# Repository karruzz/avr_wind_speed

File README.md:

# About

Wind speed measuring

# Board schematic

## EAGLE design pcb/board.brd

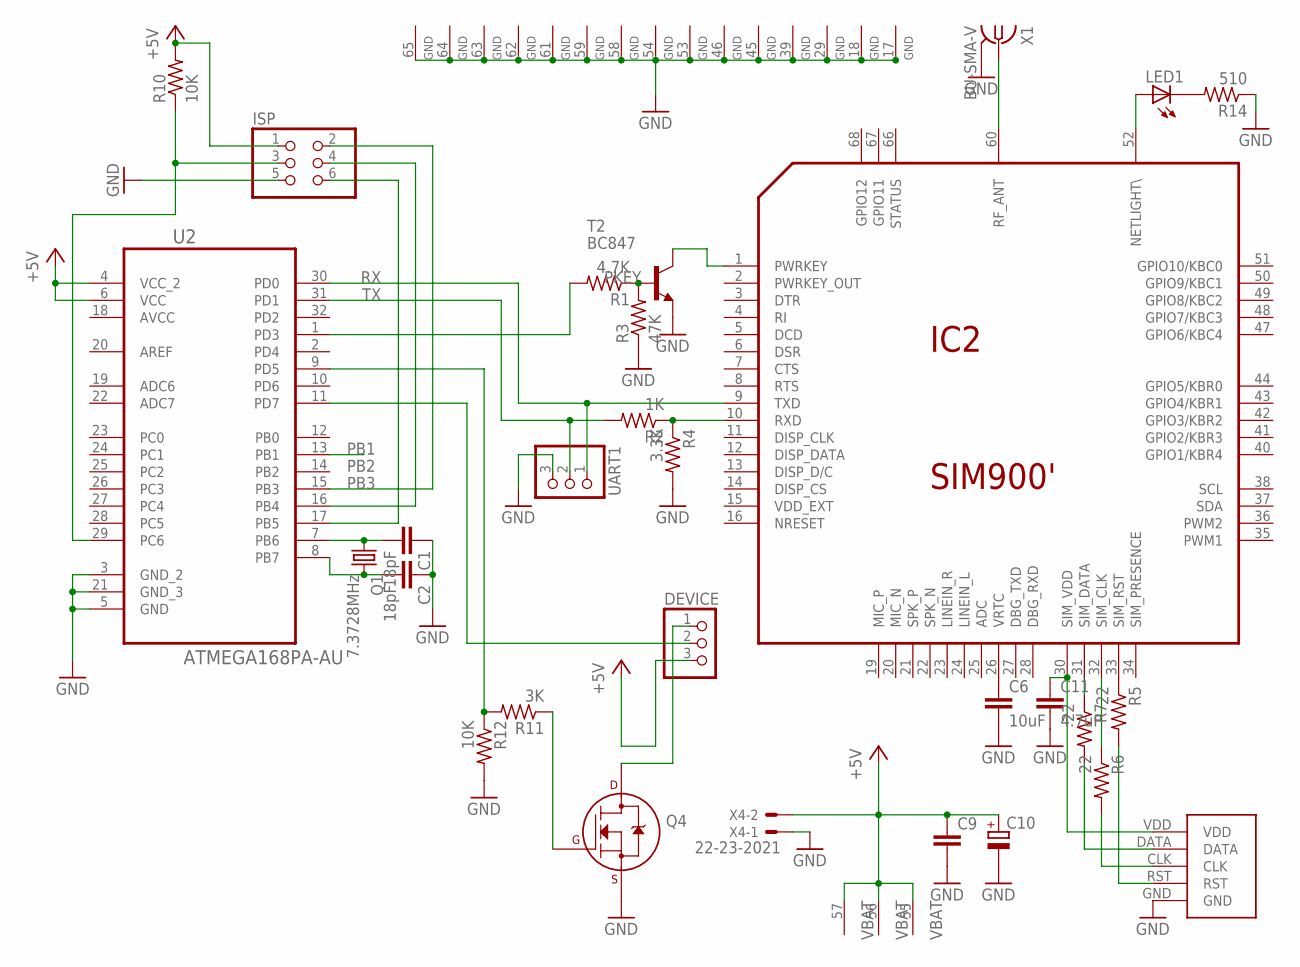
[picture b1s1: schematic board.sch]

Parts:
C1, C2: 18pF; C1206
C6: 10uF; C1206
C9: C-EUC1206K; C1206K
C10: CPOL-EUE5-8.5; E5-8,5
C11: 4.7uF; C1206
DEVICE: PINHD-1X3; 1X03
IC2: SIM900'; SIM900_NARROW
ISP: PINHD-2X3; 2X03
LED1: LED_E; LED_1206
Q1: 7.3728MHz; HC49U-V
Q4: 2N700_SOT23_1; SOT23
R1: 4.7K; R1206
R2: 1K; R1206
R3: 47K; R1206
R4: 3.3K; R1206
R5, R6, R7: 22; R1206
R10, R12: 10K; M1206
R11: 3K; M1206
R14: 510; R1206
SIM_HOLDER: 115B-AAA0-R; C707_10M006_512_2
T2: BC847; SOT23
U2: ATMEGA168PA-AU; QFP80P900X900X120-32N
UART1: PINHD-1X3; 1X03
X1: BU-SMA-V
X4: 22-23-2021

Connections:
+5V: C9.1, C10.+, DEVICE.3, IC2.55 (VBAT), IC2.56 (VBAT), IC2.57 (VBAT), ISP.1, R10.2, U2.4 (VCC_2), U2.6 (VCC), X4.2
AVCC: U2.18 (AVCC)
GND: C1.1, C2.1, C6.2, C9.2, C10.-, C11.2, IC2.17 (GND), IC2.18 (GND), IC2.29 (GND), IC2.39 (GND), IC2.45 (GND), IC2.46 (GND), IC2.53 (GND), IC2.54 (GND), IC2.58 (GND), IC2.59 (GND), IC2.61 (GND), IC2.62 (GND), IC2.63 (GND), IC2.64 (GND), IC2.65 (GND), ISP.5, Q4.2 (S), R3.1, R4.2, R12.2, R14.1, SIM_HOLDER.GND, T2.2 (E), U2.3 (GND_2), U2.5 (GND), U2.21 (GND_3), UART1.3, X1.2, X1.3 (2), X1.4 (2), X1.5 (2), X4.1
unnamed: C1.2, Q1.1, U2.7 (PB6)
unnamed: DEVICE.2, U2.11 (PD7)
unnamed: Q4.1 (G), R11.1
unnamed: ISP.3, R10.1, U2.29 (PC6)
unnamed: ISP.4, U2.16 (PB4)
unnamed: ISP.6, U2.17 (PB5)
unnamed: IC2.1 (PWRKEY), T2.3 (C)
unnamed: IC2.10 (RXD), R2.1, R4.1
unnamed: R1.1, R3.2, T2.1 (B)
unnamed: C2.2, Q1.2, U2.8 (PB7)
unnamed: IC2.52 (NETLIGHT\), LED1.A
unnamed: LED1.C, R14.2
unnamed: R5.2, SIM_HOLDER.RST
unnamed: C11.1, IC2.30 (SIM_VDD), SIM_HOLDER.VDD
unnamed: C6.1, IC2.26 (VRTC)
unnamed: IC2.31 (SIM_DATA), R7.1
unnamed: IC2.32 (SIM_CLK), R6.1
unnamed: IC2.33 (SIM_RST), R5.1
unnamed: R7.2, SIM_HOLDER.DATA
unnamed: IC2.60 (RF_ANT), X1.1
unnamed: DEVICE.1, Q4.3 (D)
unnamed: R6.2, SIM_HOLDER.CLK
PB1: U2.13 (PB1)
PB2: R11.2, R12.1, U2.9 (PD5)
PB3: ISP.2, U2.15 (PB3)
PKEY: R1.2, U2.1 (PD3)
RX: IC2.9 (TXD), U2.30 (PD0), UART1.1
TX: R2.2, U2.31 (PD1), UART1.2

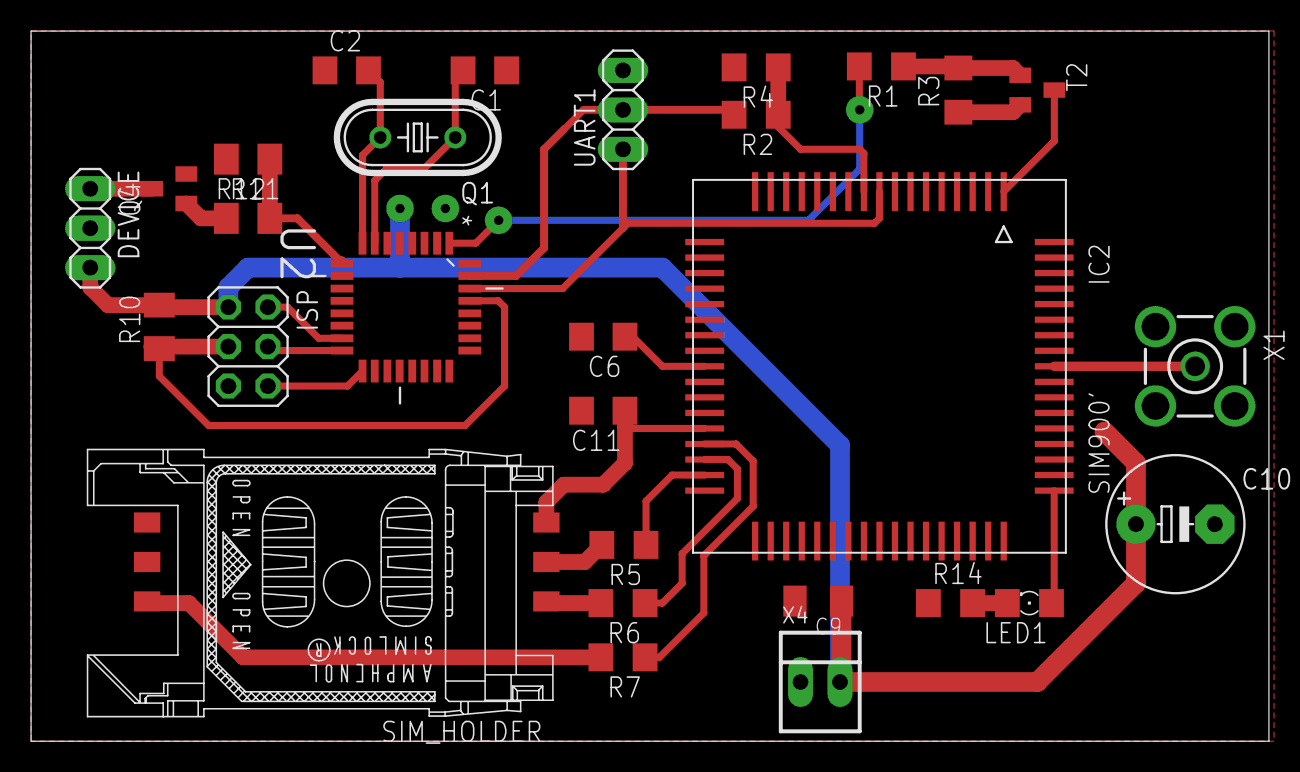
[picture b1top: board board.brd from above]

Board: 2 copper layers, 79.7 x 45.7 mm, 29 parts (0 on the bottom side), 29 nets.

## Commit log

2014-09-28 wind speed measuring
2014-09-28 strings processing
2014-10-01 sim initializing fixed (\r sends uart)
2014-10-07 36864 quarz, main loop refactoring
2014-10-08 sending data by chunks
2014-10-10 use exponential function for wind speed counting
2014-10-10 remove debug parts
2014-10-11 refactor
2014-10-14 sending raw data
2014-10-18 decreasing send buffer due to splitting url
2014-10-19 errors in receiving confirmation
2014-11-01 fixed: didn't read all data from input buffer
2014-11-01 disable debug output, 15 min sending period
2014-11-03 use invalid pin for sensor supplying
2014-11-06 linear approximation
2019-01-23 to git
2019-01-24 renamed
2019-01-30 cmake, json, downcase
2019-01-30 README
2019-02-02 img, data types
2019-02-02 https img, comment
